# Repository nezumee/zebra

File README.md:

# Zebra
Zebra, adjustable column stagger keyboard

# Overview
Zebra is a column staggered keyboard with independent PCBs for every column, allowing them to be put together in different positions or combinations without remaking any components or resoldering.

# Parts
For pictured configuration:
- Zebra head PCB x1 (see [KiCad](/PCB/Zebra) and [gerbers](/PCB/Gerber))
- Zebra stripe PCB x12. Up to 14 are supported, adjust other part counts accordingly if using more or less
- ProMicro, Elite C or equivalent x1
- ProMicro socket x1 (optional, I used https://www.digikey.com/en/products/detail/mill-max-manufacturing-corp/315-43-164-41-003000/1212143)
- 1N4148 diodes in through-hole package x48 (for example https://www.digikey.com/en/products/detail/1N4148TR/1N4148FSCT-ND/9356376?itemSeq=341430044)
- Kailh hotswap sockets x48 (optional)
- Single-line jumper wire headers x122 pins (remember every cut of header stripe means losing a pin. I bought 4x https://www.digikey.com/en/products/detail/chip-quik-inc/HDR100IMP40F-G-V-TH/5978200 and barely had any left. Get extras!)
- M/M jumper wires x65, at least 18 of them longer than 5 inches
- M/F jumper wire extender with at least 11 pins x1 (optional, to place the keyboard halves wider)
- Cherry MX switches and 1U keycaps of your choice x48
- Some way of holding the stripe PCBs in place: cardboard and sticky tape, or 3d printed enclosure, or anything else you come up with
- M2x5 screws and M2 nuts x20 (if using the 3d printed enclosure)
	
# Steps
## Solder the head PCB
1. Solder the ProMicro socket. Make sure to do it on the right side of the PCB depending on the way the pins on your ProMicro are oriented (Pin 1 is square on the PCB). My ProMicro has pins soldered so it's mounted upside down, with the MCU facing downwards
2. Solder the jumper headers on the same side

	(ignore the wires in the picture)
	
## Solder the stripes
Solder the diodes, switch sockets and jumper headers

You can skip soldering the diodes and sockets if you're not planning to use some switches (lower left).
	
## Connect the boards
Here's how the wires must be connected:
- Head

	Note that the row wires are different between the left and right sides, don't connect them to each other!

- Stripes

- Overview of connections:

- When connecting row wires between stripes, use the headers that are further apart so that the wires don't need to bend as much when the columns are arranged next to each other:

## Arrange the boards
Now the difficult part - putting the stripes in place.

- Option 1: cut the shape out of cardboard that you want to place the stripes in, put some sticky tape at the back (glue side up), and stick the column boards to it:

	A template is available in [cardboard.svg](/Case/Cardboard.svg) file.
	
- Option 2: 3d print [stripe holders](/Case/3d-printed.stl), screw them together and insert the stripe PCBs:

	Note that a stripe allows changing stagger between 10mm in one direction and 20mm in another. Mirror half the stripes to flip which way gets more stagger on different sides of the keyboard.
	
	A basic ruler is built into the bottom of each stripe to measure the column stagger:

# Firmware
Zebra is running QMK, see the source code under the QMK folder. Copy the [zebra](/QMK/zebra) folder under the keyboards folder in your QMK environment to compile. You can use JSON layout files made for Corne (LAYOUT_split_3x6_3) to build your layout in QMK configurator.

# Have fun
Try some popular or crazy configurations and see what you like!

Here's some examples:

- Let's split: no stagger

- Corne: index finger +2.4mm/middle +2.4mm/ring -2.4mm/pinky -4.8mm

- Kyria: +2.5mm/+6.5mm/-6mm/-12mm

- More aggressive stagger: +2.5mm/+10mm/-5mm/-14mm

- Tenting, encoders, true split and more in v2!

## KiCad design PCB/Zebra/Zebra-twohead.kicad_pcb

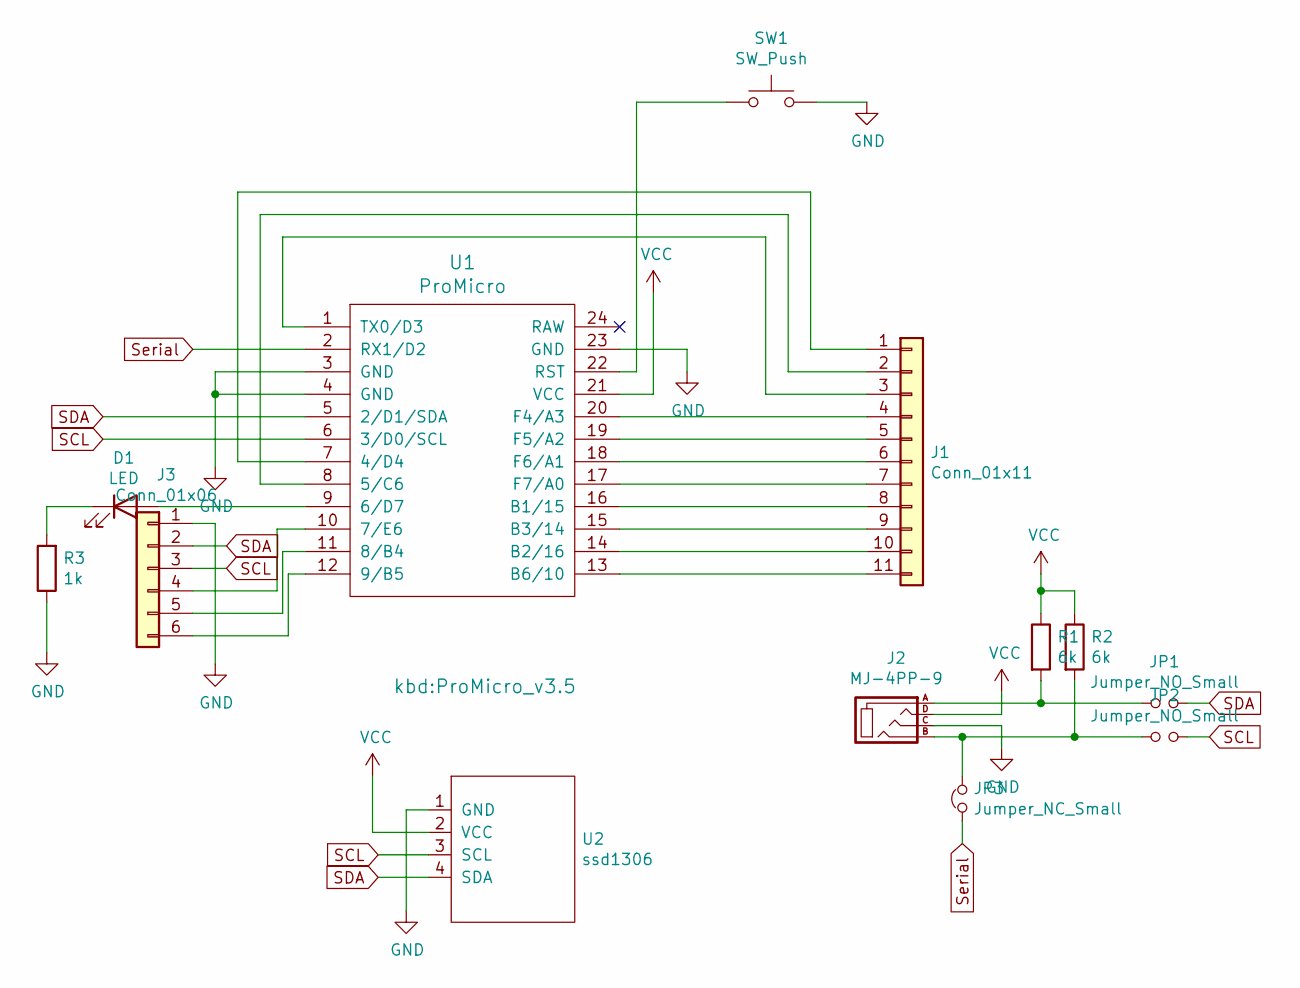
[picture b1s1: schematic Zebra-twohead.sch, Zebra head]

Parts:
D1: LED; LED_D3.0mm
J1: Conn_01x11; PinHeader_1x11_P2.54mm_Vertical
J2: MJ-4PP-9; MJ-4PP-9_1side
J3: Conn_01x06; PinHeader_1x06_P2.54mm_Vertical
JP1, JP2: Jumper_NO_Small; SolderJumper-2_P1.3mm_Open_Pad1.0x1.5mm
JP3: Jumper_NC_Small; SolderJumper-2_P1.3mm_Bridged_Pad1.0x1.5mm
R1, R2: 6k; R_1206_3216Metric_Pad1.30x1.75mm_HandSolder
R3: 1k; R_1206_3216Metric_Pad1.30x1.75mm_HandSolder
SW1: SW_Push; ResetSW_1side
U1: ProMicro; ProMicro_v3.5
U2: ssd1306; SSD1306

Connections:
GND: J2.C, J3.1, R3.1, SW1.2, U1.3 (GND), U1.4 (GND), U1.23 (GND), U2.1 (GND)
unnamed: D1.1 (K), R3.2
unnamed: D1.2 (A), U1.9 (6/D7)
unnamed: J1.1, U1.7 (4/D4)
unnamed: J1.2, U1.8 (5/C6)
unnamed: J1.3, U1.1 (TX0/D3)
unnamed: J1.4, U1.20 (F4/A3)
unnamed: J1.5, U1.19 (F5/A2)
unnamed: J1.6, U1.18 (F6/A1)
unnamed: J1.7, U1.17 (F7/A0)
unnamed: J1.8, U1.16 (B1/15)
unnamed: J1.9, U1.15 (B3/14)
unnamed: J1.10, U1.14 (B2/16)
unnamed: J1.11, U1.13 (B6/10)
unnamed: J2.A, JP1.1, R1.2
unnamed: J2.B, JP2.1, JP3.2, R2.2
unnamed: J3.4, U1.10 (7/E6)
unnamed: J3.5, U1.11 (8/B4)
unnamed: J3.6, U1.12 (9/B5)
unnamed: SW1.1, U1.22 (RST)
SCL: J3.3, JP2.2, U1.6 (3/D0/SCL), U2.3 (SCL)
SDA: J3.2, JP1.2, U1.5 (2/D1/SDA), U2.4 (SDA)
Serial: JP3.1, U1.2 (RX1/D2)
VCC: J2.D, R1.1, R2.1, U1.21 (VCC), U2.2 (VCC)

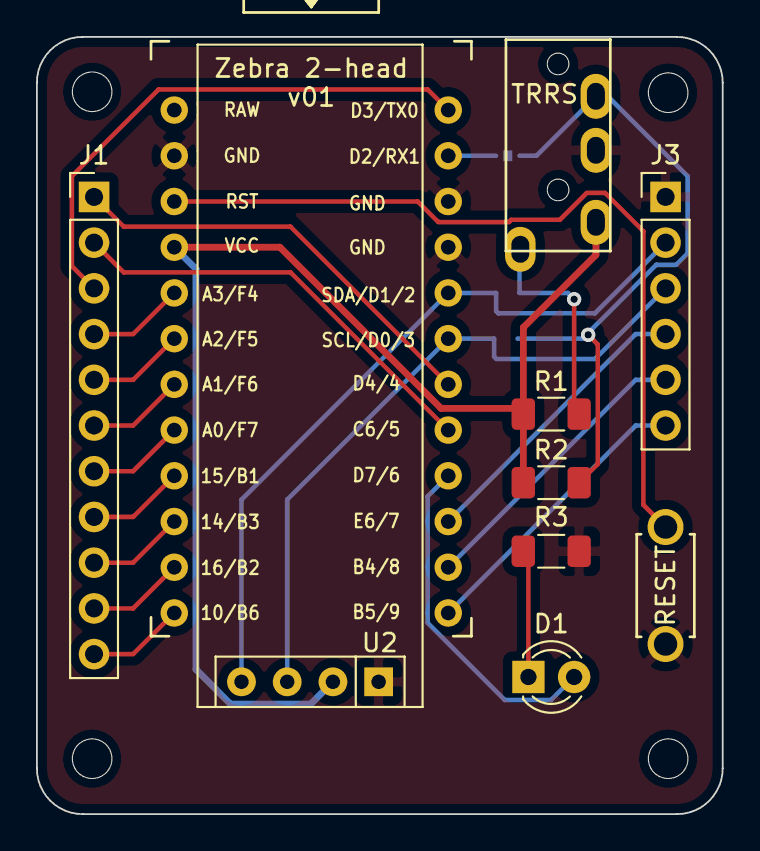
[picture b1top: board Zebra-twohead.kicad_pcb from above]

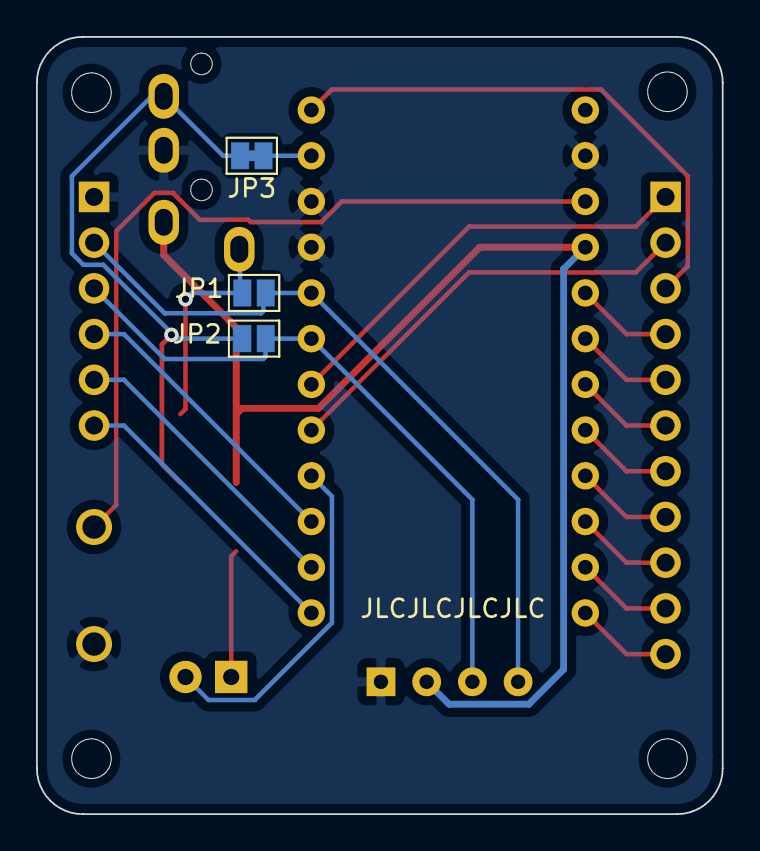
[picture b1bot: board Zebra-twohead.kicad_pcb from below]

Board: 2 copper layers, 38.1 x 43.2 mm, 13 parts (3 on the bottom side), 24 nets.

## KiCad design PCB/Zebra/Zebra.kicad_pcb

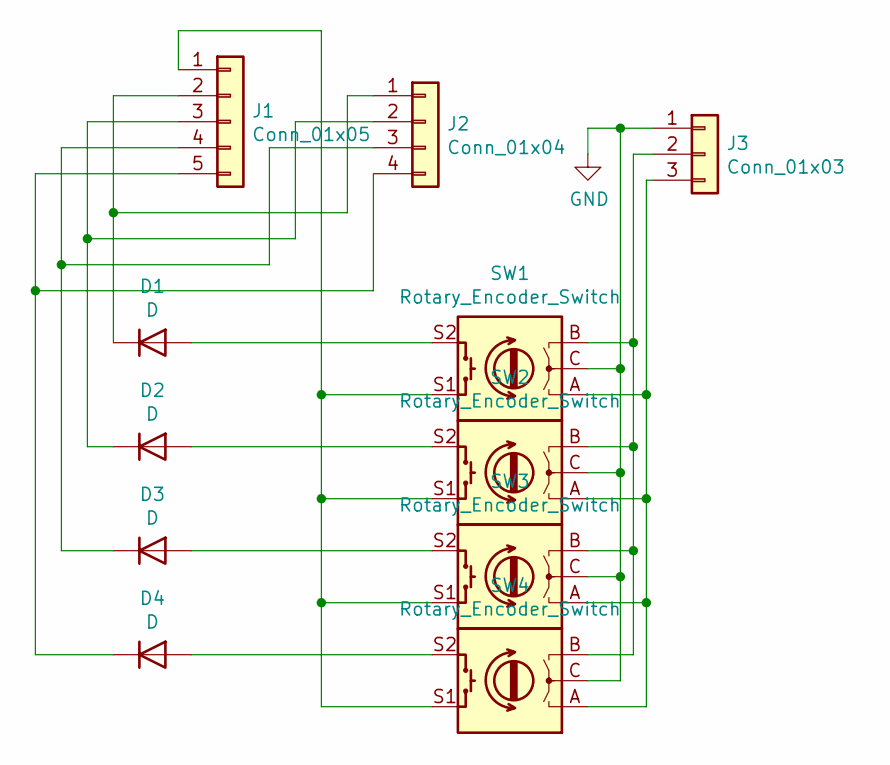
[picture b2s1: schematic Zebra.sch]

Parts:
D1, D2, D3, D4: D; D_DO-34_SOD68_P7.62mm_Horizontal
J1: Conn_01x05; PinHeader_1x05_P2.54mm_Vertical
J2: Conn_01x04; PinHeader_1x04_P2.54mm_Vertical
J3: Conn_01x03; PinHeader_1x03_P2.54mm_Vertical
SW1, SW2, SW3, SW4: Rotary_Encoder_Switch; CherryMX_Hotswap_Encoder

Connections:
GND: J3.1, SW1.C, SW2.C, SW3.C, SW4.C
unnamed: D1.1 (K), J1.2, J2.1
unnamed: D1.2 (A), SW1.S2
unnamed: D2.1 (K), J1.3, J2.2
unnamed: D2.2 (A), SW2.S2
unnamed: D3.1 (K), J1.4, J2.3
unnamed: D3.2 (A), SW3.S2
unnamed: D4.1 (K), J1.5, J2.4
unnamed: D4.2 (A), SW4.S2
unnamed: J1.1, SW1.S1, SW2.S1, SW3.S1, SW4.S1
unnamed: J3.2, SW1.B, SW2.B, SW3.B, SW4.B
unnamed: J3.3, SW1.A, SW2.A, SW3.A, SW4.A

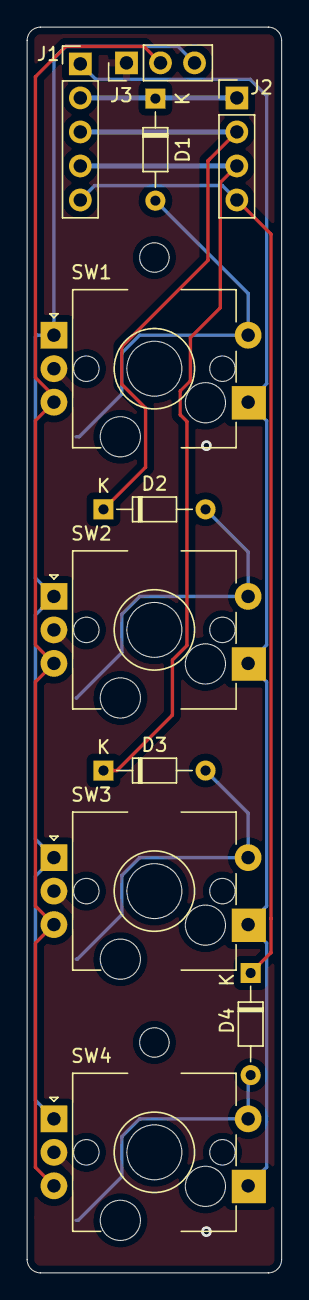
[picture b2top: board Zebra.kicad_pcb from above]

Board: 2 copper layers, 19.0 x 93.0 mm, 12 parts (0 on the bottom side), 12 nets.

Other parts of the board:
 : MountingHole_2.2mm_M2

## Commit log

2020-12-06 Add keyboard files
2020-12-06 Add images
2020-12-06 Update images
2020-12-07 Add case files and examples
2020-12-09 Switch to foostan's footprint library, MIT license
2020-12-09 Remove backup and cache files
2020-12-09 Add TRRS jack
    With serial and optional I2C
2020-12-09 Revert "Add TRRS jack"
    This reverts commit 0ecc4aa986bd018de9fb38d5a9cbe8efcda9557b.
2020-12-09 Add Zebra 2-head separately
2020-12-09 Add encoders
2020-12-09 Rename switches, renumber
2020-12-09 Add mounting holes to the stripe
2020-12-09 Ignore autosave files
2020-12-10 Add extra connector, LED, clean up
2020-12-10 Make gerbers
2021-02-27 Add tenting, angled, thumb stripe models
2021-02-27 Add v2 teaser
2021-02-27 Resize image
2021-02-27 Add Zebra v2 firmware
